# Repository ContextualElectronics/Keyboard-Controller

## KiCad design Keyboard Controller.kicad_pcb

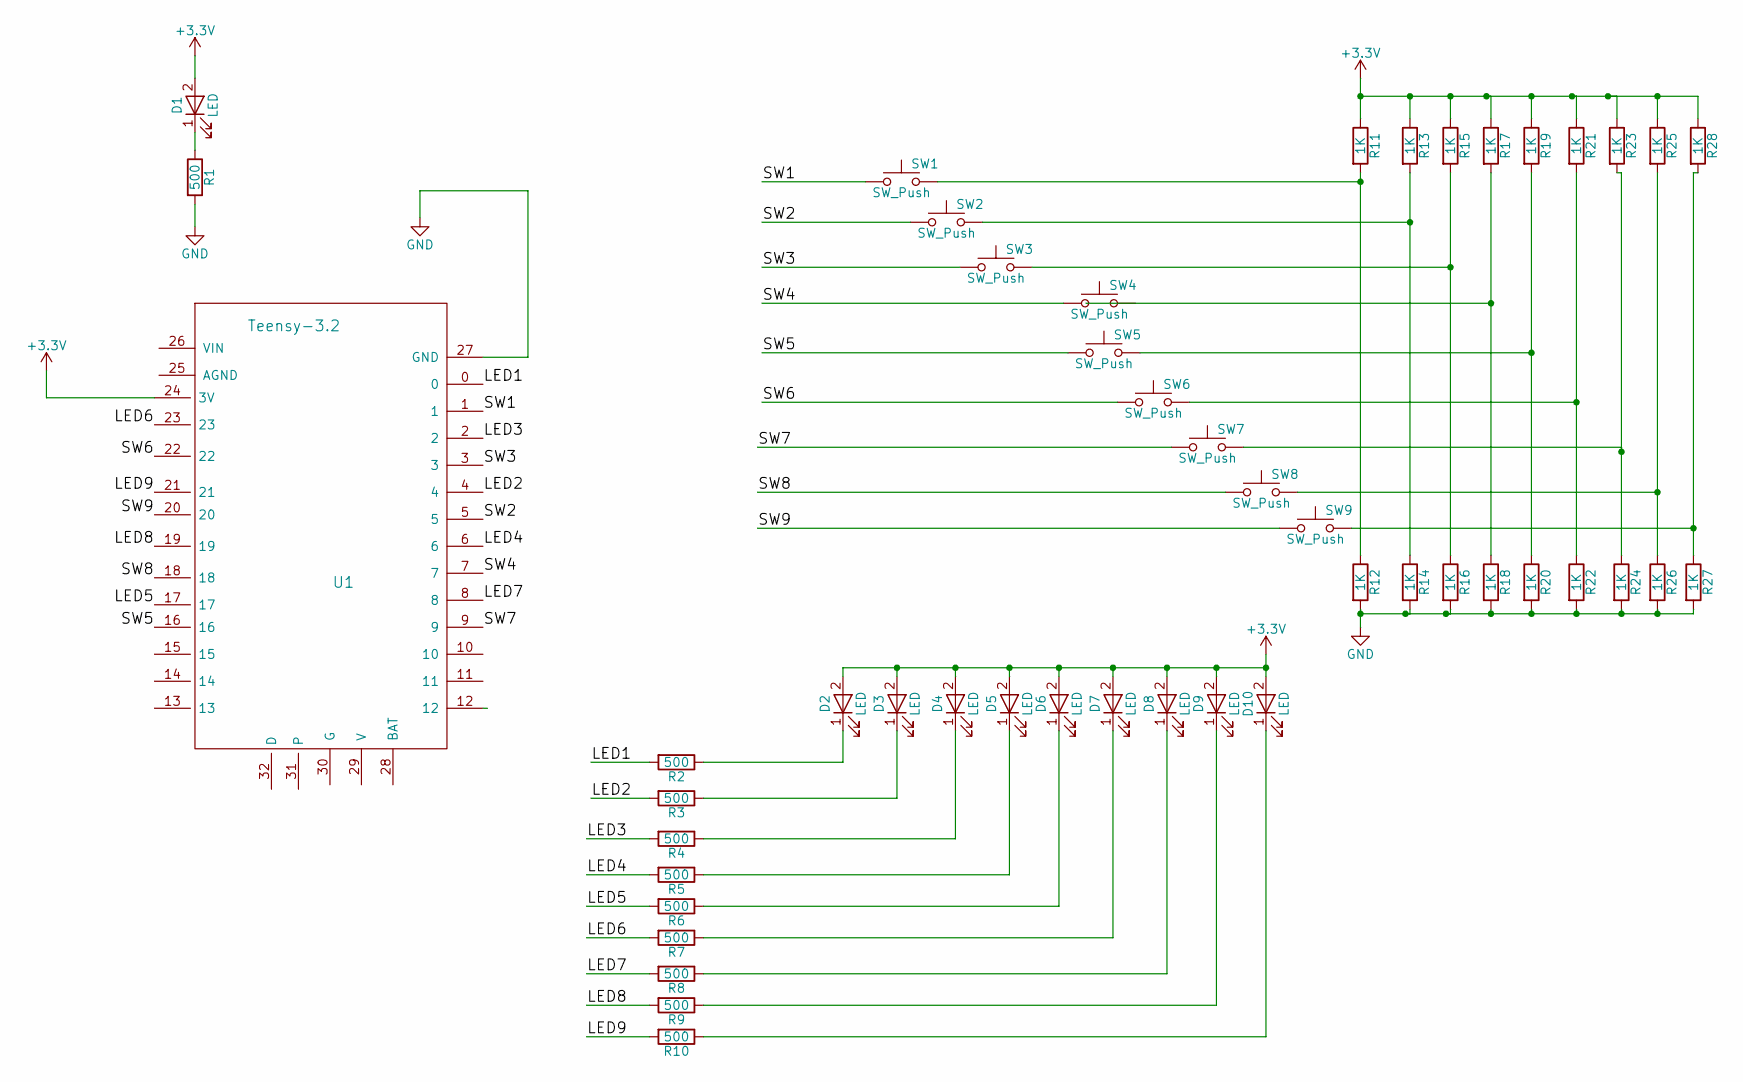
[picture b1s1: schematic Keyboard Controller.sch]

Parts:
D1, D2, D3, D4, D5, D6, D7, D8, D9, D10: LED; LED_0805
R1, R2, R3, R4, R5, R6, R7, R8, R9, R10: 500; R_0805_HandSoldering
R11, R12, R13, R14, R15, R16, R17, R18, R19, R20, R21, R22, R23, R24, R25, R26, R27, R28: 1K; R_0805_HandSoldering
SW1, SW2, SW3, SW4, SW5, SW6, SW7, SW8, SW9: SW_Push; PTS645SK43SMTR92; MPN PTS645SK43SMTR92
U1: Teensy-3.2; Teensy-32

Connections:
+3V3: D1.2 (A), D2.2 (A), D3.2 (A), D4.2 (A), D5.2 (A), D6.2 (A), D7.2 (A), D8.2 (A), D9.2 (A), D10.2 (A), R11.1, R13.1, R15.1, R17.1, R19.1, R21.1, R23.1, R25.1, R28.1, U1.24 (3V)
/LED1: R2.2, U1.0
/LED2: R3.2, U1.4
/LED3: R4.2, U1.2
/LED4: R5.2, U1.6
/LED5: R6.2, U1.17
/LED6: R7.2, U1.23
/LED7: R8.2, U1.8
/LED8: R9.2, U1.19
/LED9: R10.2, U1.21
/SW1: SW1.1, U1.1
/SW2: SW2.1, U1.5
/SW3: SW3.1, U1.3
/SW4: SW4.1, U1.7
/SW5: SW5.1, U1.16
/SW6: SW6.1, U1.22
/SW7: SW7.1, U1.9
/SW8: SW8.1, U1.18
/SW9: SW9.1, U1.20
GND: R1.2, R12.2, R14.2, R16.2, R18.2, R20.2, R22.2, R24.2, R26.2, R27.2, U1.27 (GND)
unnamed: D1.1 (K), R1.1
unnamed: D2.1 (K), R2.1
unnamed: D3.1 (K), R3.1
unnamed: D4.1 (K), R4.1
unnamed: D5.1 (K), R5.1
unnamed: D6.1 (K), R6.1
unnamed: D7.1 (K), R7.1
unnamed: D8.1 (K), R8.1
unnamed: D9.1 (K), R9.1
unnamed: D10.1 (K), R10.1
unnamed: R11.2, R12.1, SW1.2
unnamed: R13.2, R14.1, SW2.2
unnamed: R15.2, R16.1, SW3.2
unnamed: R19.2, R20.1, SW5.2
unnamed: R21.2, R22.1, SW6.2
unnamed: R23.2, R24.1, SW7.2
unnamed: R25.2, R26.1, SW8.2
unnamed: R27.1, R28.2, SW9.2

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
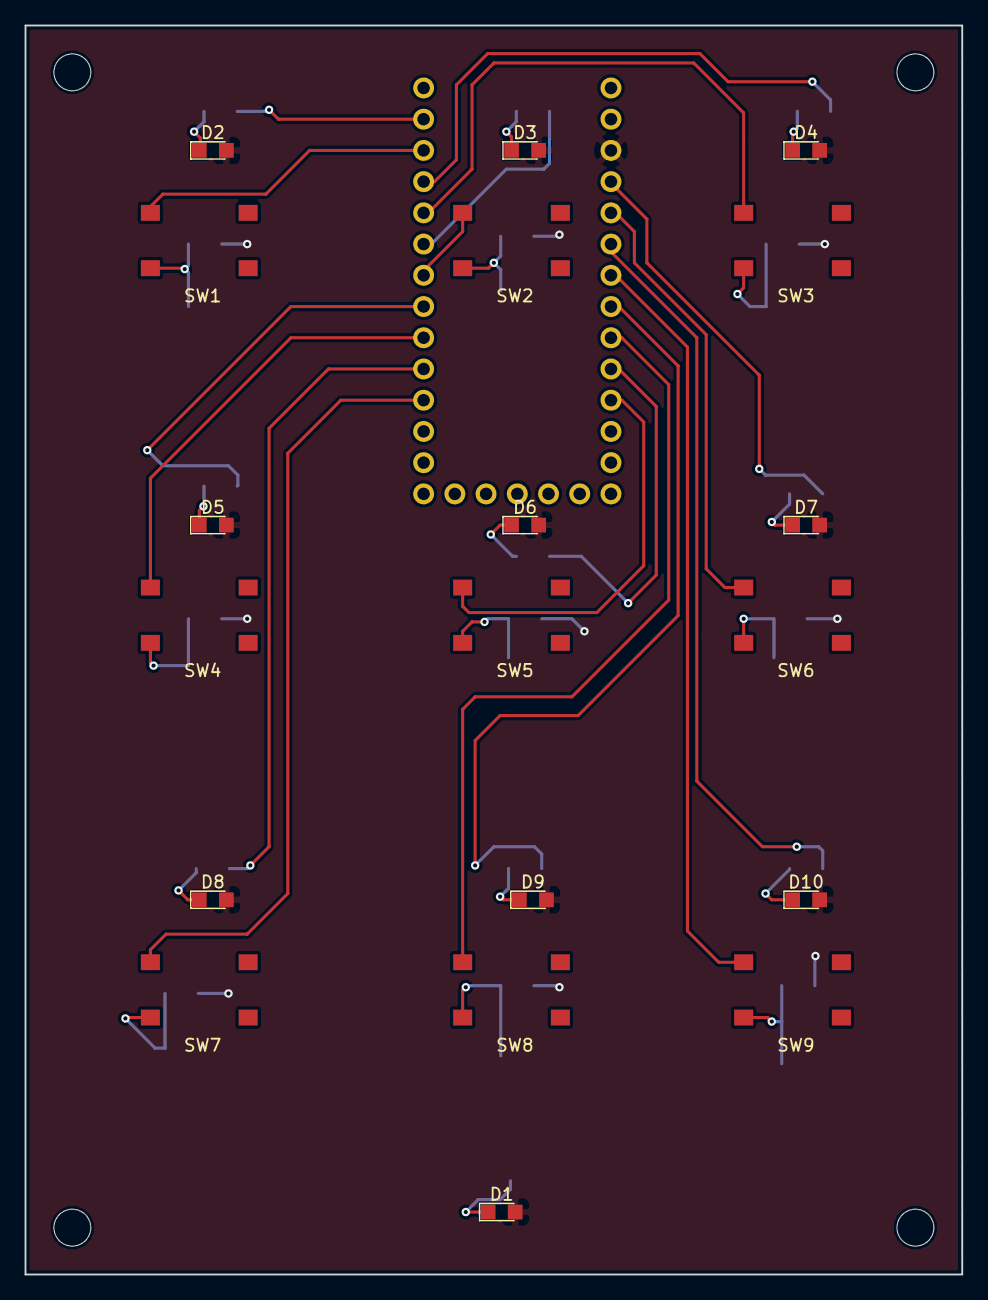
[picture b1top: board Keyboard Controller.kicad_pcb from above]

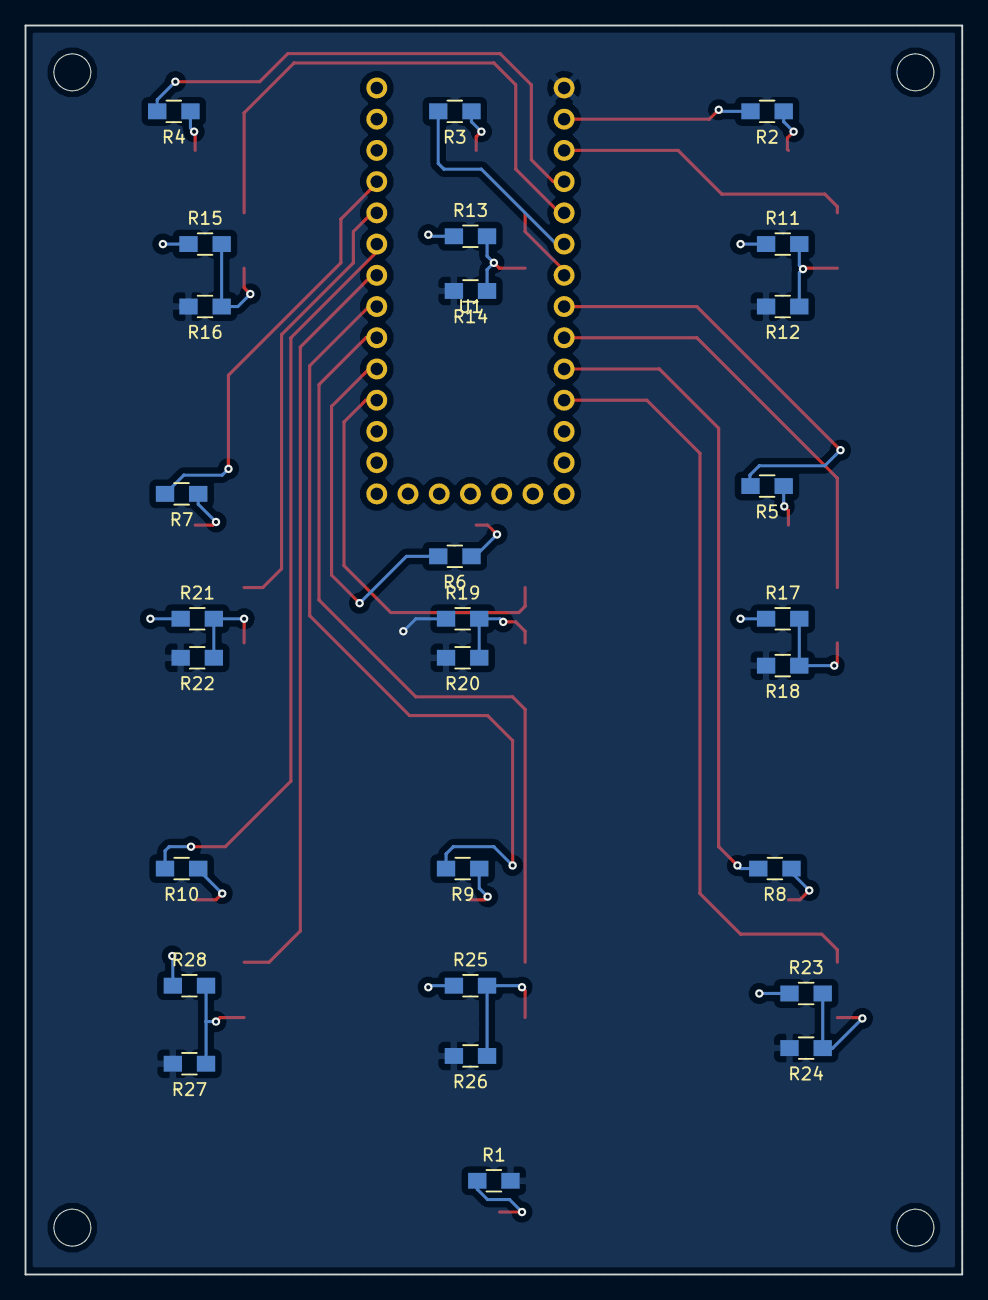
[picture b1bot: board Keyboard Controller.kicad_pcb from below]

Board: 2 copper layers, 76.2 x 101.6 mm, 48 parts (29 on the bottom side), 39 nets.

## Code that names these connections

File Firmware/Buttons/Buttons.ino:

/* Buttons to USB Keyboard Example

   You must select Keyboard from the "Tools > USB Type" menu

   This example code is in the public domain.
*/

#include <Bounce.h>

// Create Bounce objects for each button.  The Bounce object
// automatically deals with contact chatter or "bounce", and
// it makes detecting changes very simple.
Bounce button0 = Bounce(0, 10);
Bounce button1 = Bounce(1, 10);  // 10 = 10 ms debounce time
Bounce button2 = Bounce(2, 10);  // which is appropriate for
Bounce button3 = Bounce(3, 10);  // most mechanical pushbuttons
Bounce button4 = Bounce(4, 10);
Bounce button5 = Bounce(5, 10);  // if a button is too "sensitive"
Bounce button6 = Bounce(6, 10);  // to rapid touch, you can
Bounce button7 = Bounce(7, 10);  // increase this time.
Bounce button8 = Bounce(8, 10);
Bounce button9 = Bounce(9, 10);

int LED1 = 0;
int LED2 = 4;
int LED3 = 2;
int LED4 = 6;
int LED5 = 17;
int LED6 = 23;
int LED7 = 8;
int LED8 = 19;
int LED9 = 21;
int SW1 = 1;
int SW2 = 5;
int SW3 = 3;
int SW4 = 7;
int SW5 = 16;
int SW6 = 22;
int SW7 = 9;
int SW8 = 18;
int SW9 = 20;

void setup() {
  // Configure the pins for input mode with pullup resistors.
  // The pushbuttons connect from each pin to ground.  When
  // the button is pressed, the pin reads LOW because the button
  // shorts it to ground.  When released, the pin reads HIGH
  // because the pullup resistor connects to +5 volts inside
  // the chip.  LOW for "on", and HIGH for "off" may seem
  // backwards, but using the on-chip pullup resistors is very
  // convenient.  The scheme is called "active low", and it's
  // very commonly used in electronics... so much that the chip
  // has built-in pullup resistors!
  pinMode(0, INPUT_PULLUP);
  pinMode(1, INPUT_PULLUP);
  pinMode(2, INPUT_PULLUP);
  pinMode(3, INPUT_PULLUP);
  pinMode(4, INPUT_PULLUP);
  pinMode(5, INPUT_PULLUP);
  pinMode(6, INPUT_PULLUP);  // Teensy++ LED, may need 1k resistor pullup
  pinMode(7, INPUT_PULLUP);
  pinMode(8, INPUT_PULLUP);
  pinMode(9, INPUT_PULLUP);
}

void loop() {
  // Update all the buttons.  There should not be any long
  // delays in loop(), so this runs repetitively at a rate
  // faster than the buttons could be pressed and released.
  button0.update();
  button1.update();
  button2.update();
  button3.update();
  button4.update();
  button5.update();
  button6.update();
  button7.update();
  button8.update();
  button9.update();

  // Check each button for "falling" edge.
  // Type a message on the Keyboard when each button presses
  // Update the Joystick buttons only upon changes.
  // falling = high (not pressed - voltage from pullup resistor)
  //           to low (pressed - button connects pin to ground)
  if (button0.fallingEdge()) {
    Keyboard.println("B0 press");
  }
  if (button1.fallingEdge()) {
    Keyboard.println("B1 press");
  }
  if (button2.fallingEdge()) {
    Keyboard.println("B2 press");
  }
  if (button3.fallingEdge()) {
    Keyboard.println("B3 press");
  }
  if (button4.fallingEdge()) {
    Keyboard.println("B4 press");
  }
  if (button5.fallingEdge()) {
    Keyboard.println("B5 press");
  }
  if (button6.fallingEdge()) {
    Keyboard.println("B6 press");
  }
  if (button7.fallingEdge()) {
    Keyboard.println("B7 press");
  }
  if (button8.fallingEdge()) {
    Keyboard.println("B8 press");
  }
  if (button9.fallingEdge()) {
    Keyboard.println("B9 press");
  }

  // Check each button for "rising" edge
  // Type a message on the Keyboard when each button releases.
  // For many types of projects, you only care when the button
  // is pressed and the release isn't needed.
  // rising = low (pressed - button connects pin to ground)
  //          to high (not pressed - voltage from pullup resistor)
  if (button0.risingEdge()) {
    Keyboard.println("B0 release");
  }
  if (button1.risingEdge()) {
    Keyboard.println("B1 release");
  }
  if (button2.risingEdge()) {
    Keyboard.println("B2 release");
  }
  if (button3.risingEdge()) {
    Keyboard.println("B3 release");
  }
  if (button4.risingEdge()) {
    Keyboard.println("B4 release");
  }
  if (button5.risingEdge()) {
    Keyboard.println("B5 release");
  }
  if (button6.risingEdge()) {
    Keyboard.println("B6 release");
  }
  if (button7.risingEdge()) {
    Keyboard.println("B7 release");
  }
  if (button8.risingEdge()) {
    Keyboard.println("B8 release");
  }
  if (button9.risingEdge()) {
    Keyboard.println("B9 release");
  }
}

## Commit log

2017-01-03 Added an LED
2017-01-03 Added Teensy Library and created schematic
2017-01-03 Added indicator LEDs
2017-01-03 Generated Netlist
2017-01-03 Added Teensy Footprint
2017-01-03 Imported footprints into layout
2017-01-03 Moving components before changing LED ref des index
2017-01-03 Changed LED ref des indexing
2017-01-03 Rough placement of all components except mounting holes
2017-01-03 All placements finalized
2017-01-04 Changed pinout for easier layout
2017-01-04 Fixed ERC error
2017-01-04 Moved all non power traces to top side
2017-01-04 Finished preliminary layout
2017-01-05 Moved silkscreen into place
2017-01-05 Finished DRC, readied board for submitting to order
2017-02-06 Split folders into firmware and hardware
